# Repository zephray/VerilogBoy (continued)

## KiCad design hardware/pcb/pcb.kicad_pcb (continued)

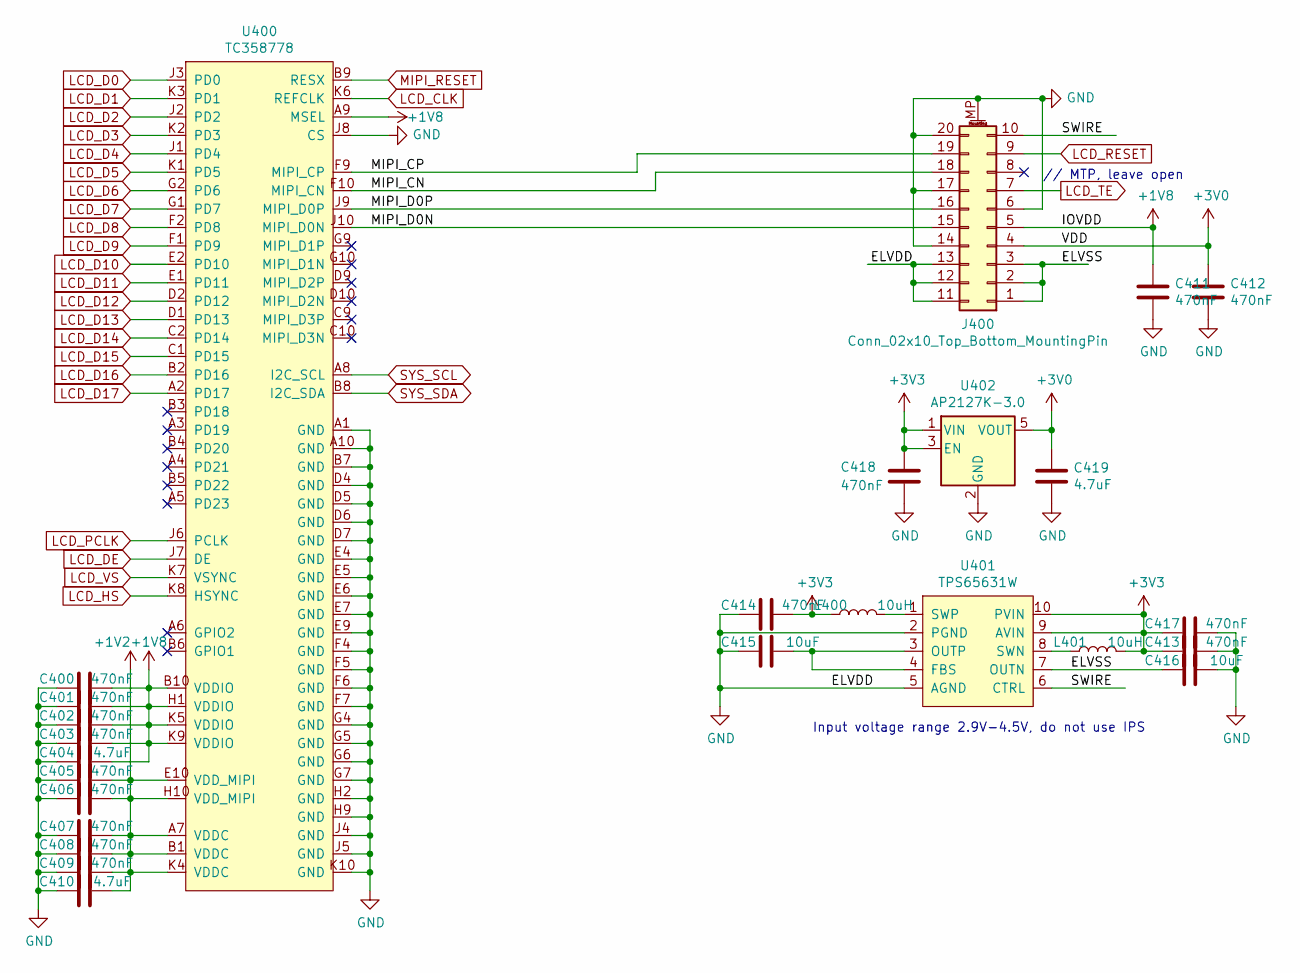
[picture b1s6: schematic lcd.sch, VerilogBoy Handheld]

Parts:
C400, C401, C402, C403, C405, C406, C407, C408, C409, C411, C412, C413, C414, C417, C418: 470nF; C_0402_1005Metric
C404, C410, C419: 4.7uF; C_0603_1608Metric
C415, C416: 10uF; C_0603_1608Metric
J400: Conn_02x10_Top_Bottom_MountingPin; AXE520124
L400, L401: 10uH; L_Vishay_IHLP-1212
U400: TC358778; BGA-80_10x10_7.0x7.0mm
U401: TPS65631W; DFN-10-1EP_3x3mm_P0.5mm_EP1.55x2.48mm
U402: AP2127K-3.0; SOT-23-5

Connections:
+1V2: C405.1, C406.1, C407.1, C408.1, C409.1, C410.1, U400.A7 (VDDC), U400.B1 (VDDC), U400.E10 (VDD_MIPI), U400.H10 (VDD_MIPI), U400.K4 (VDDC); also elsewhere on the board
+1V8: C400.1, C401.1, C402.1, C403.1, C404.1, C411.1, J400.5, U400.A9 (MSEL), U400.B10 (VDDIO), U400.H1 (VDDIO), U400.K5 (VDDIO), U400.K9 (VDDIO); also elsewhere on the board
+3V0: C412.1, C419.1, J400.4, U402.5 (VOUT)
+3V3: C413.2, C414.1, C417.2, C418.1, L400.1, L401.2, U401.9 (AVIN), U401.10 (PVIN), U402.1 (VIN), U402.3 (EN); also elsewhere on the board
/lcd/ELVSS: C416.2, J400.1, J400.2, J400.3, U401.7 (OUTN)
/lcd/MIPI_CN: J400.18, U400.F10 (MIPI_CN)
/lcd/MIPI_CP: J400.19, U400.F9 (MIPI_CP)
/lcd/MIPI_D0N: J400.15, U400.J10 (MIPI_D0N)
/lcd/MIPI_D0P: J400.16, U400.J9 (MIPI_D0P)
/lcd/SWIRE: J400.10, U401.6 (CTRL)
GND: C400.2, C401.2, C402.2, C403.2, C404.2, C405.2, C406.2, C407.2, C408.2, C409.2, C410.2, C411.2, C412.2, C413.1, C414.2, C415.2, C416.1, C417.1, C418.2, C419.2, J400.6, J400.11, J400.12, J400.13, J400.14, J400.17, J400.20, J400.MP (MountPin), U400.A1 (GND), U400.A10 (GND), U400.B7 (GND), U400.D4 (GND), U400.D5 (GND), U400.D6 (GND), U400.D7 (GND), U400.E4 (GND), U400.E5 (GND), U400.E6 (GND), U400.E7 (GND), U400.E9 (GND), U400.F4 (GND), U400.F5 (GND), U400.F6 (GND), U400.F7 (GND), U400.G4 (GND), U400.G5 (GND), U400.G6 (GND), U400.G7 (GND), U400.H2 (GND), U400.H9 (GND), U400.J4 (GND), U400.J5 (GND), U400.J8 (CS), U400.K10 (GND), U401.2 (PGND), U401.5 (AGND), U402.2 (GND); also elsewhere on the board
LCD_CLK: U400.K6 (REFCLK); also elsewhere on the board
LCD_D0: U400.J3 (PD0); also elsewhere on the board
LCD_D1: U400.K3 (PD1); also elsewhere on the board
LCD_D2: U400.J2 (PD2); also elsewhere on the board
LCD_D4: U400.J1 (PD4); also elsewhere on the board
LCD_D5: U400.K1 (PD5); also elsewhere on the board
LCD_D6: U400.G2 (PD6); also elsewhere on the board
LCD_D7: U400.G1 (PD7); also elsewhere on the board
LCD_D8: U400.F2 (PD8); also elsewhere on the board
LCD_D9: U400.F1 (PD9); also elsewhere on the board
LCD_D10: U400.E2 (PD10); also elsewhere on the board
LCD_D11: U400.E1 (PD11); also elsewhere on the board
LCD_D12: U400.D2 (PD12); also elsewhere on the board
LCD_D13: U400.D1 (PD13); also elsewhere on the board
LCD_D14: U400.C2 (PD14); also elsewhere on the board
LCD_D15: U400.C1 (PD15); also elsewhere on the board
LCD_D16: U400.B2 (PD16); also elsewhere on the board
LCD_D17: U400.A2 (PD17); also elsewhere on the board
LCD_DE: U400.J7 (DE); also elsewhere on the board
LCD_PCLK: U400.J6 (PCLK); also elsewhere on the board
LCD_RESET: J400.9; also elsewhere on the board
LCD_TE: J400.7; also elsewhere on the board
LCD_VS: U400.K7 (VSYNC); also elsewhere on the board
unnamed: C415.1, U401.3 (OUTP), U401.4 (FBS)
unnamed: L400.2, U401.1 (SWP)
unnamed: L401.1, U401.8 (SWN)
SYS_SCL: U400.A8 (I2C_SCL); also elsewhere on the board
SYS_SDA: U400.B8 (I2C_SDA); also elsewhere on the board

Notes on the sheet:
Input voltage range 2.9V-4.5V, do not use IPS
// MTP, leave open

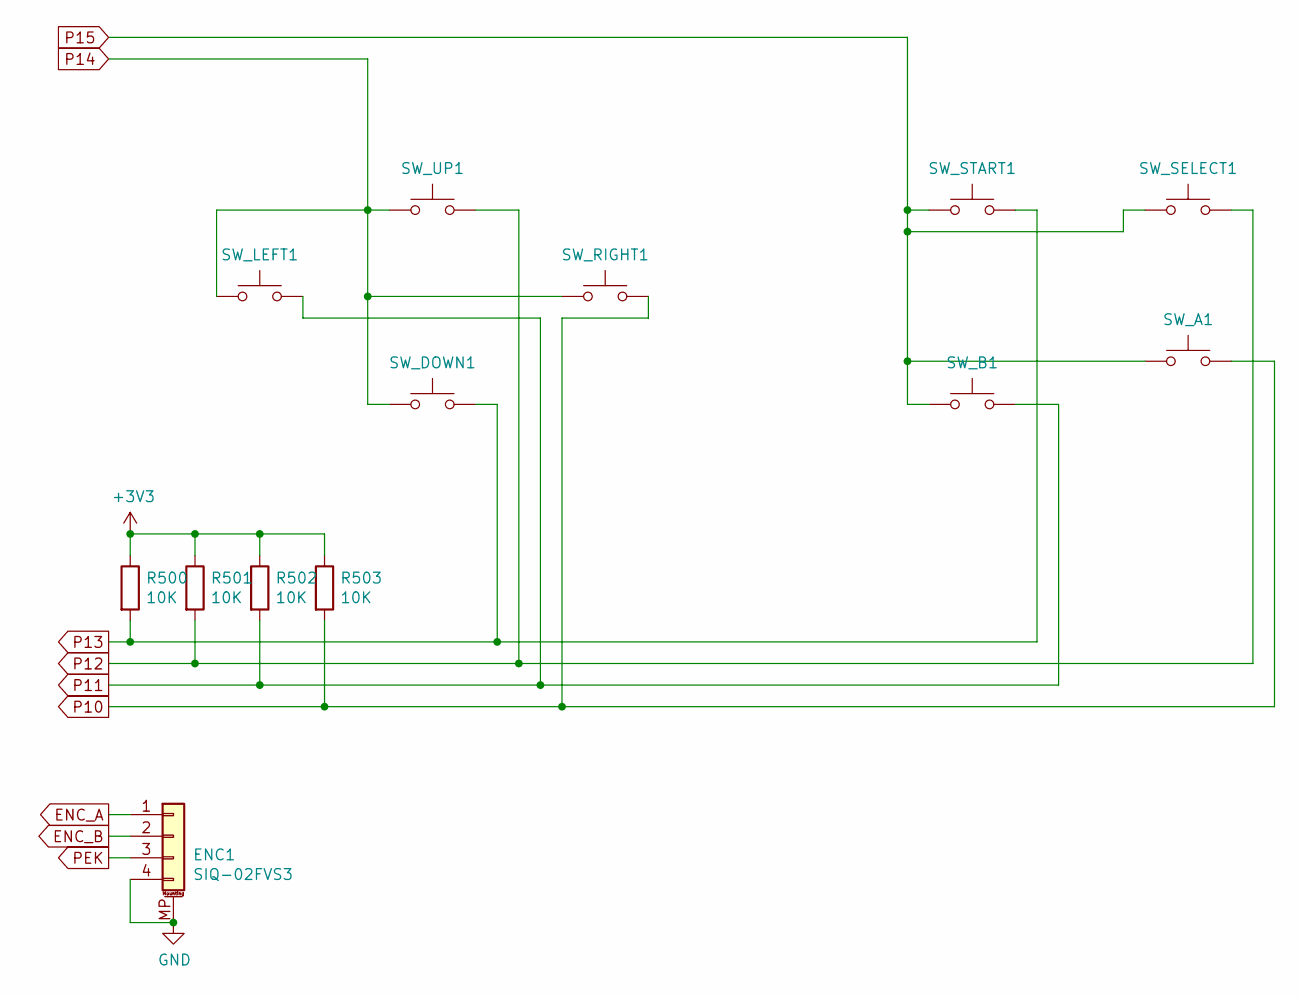
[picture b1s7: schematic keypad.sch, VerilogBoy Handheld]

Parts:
ENC1: SIQ-02FVS3
R500, R501, R502, R503: 10K; R_0402_1005Metric
SW_A1: SW_Push; Contact_4mm
SW_B1: SW_Push; Contact_4mm
SW_DOWN1: SW_Push; Contact_4mm
SW_LEFT1: SW_Push; Contact_4mm
SW_RIGHT1: SW_Push; Contact_4mm
SW_SELECT1: SW_Push; Contact_4mm
SW_START1: SW_Push; Contact_4mm
SW_UP1: SW_Push; Contact_4mm

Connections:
+3V3: R500.1, R501.1, R502.1, R503.1; also elsewhere on the board
ENC_A: ENC1.1; also elsewhere on the board
ENC_B: ENC1.2; also elsewhere on the board
GND: ENC1.4, ENC1.MP (MountPin); also elsewhere on the board
P10: R503.2, SW_A1.2, SW_RIGHT1.2; also elsewhere on the board
P11: R502.2, SW_B1.2, SW_LEFT1.2; also elsewhere on the board
P12: R501.2, SW_SELECT1.2, SW_UP1.2; also elsewhere on the board
P13: R500.2, SW_DOWN1.2, SW_START1.2; also elsewhere on the board
P14: SW_DOWN1.1, SW_LEFT1.1, SW_RIGHT1.1, SW_UP1.1; also elsewhere on the board
P15: SW_A1.1, SW_B1.1, SW_SELECT1.1, SW_START1.1; also elsewhere on the board
PEK: ENC1.3; also elsewhere on the board

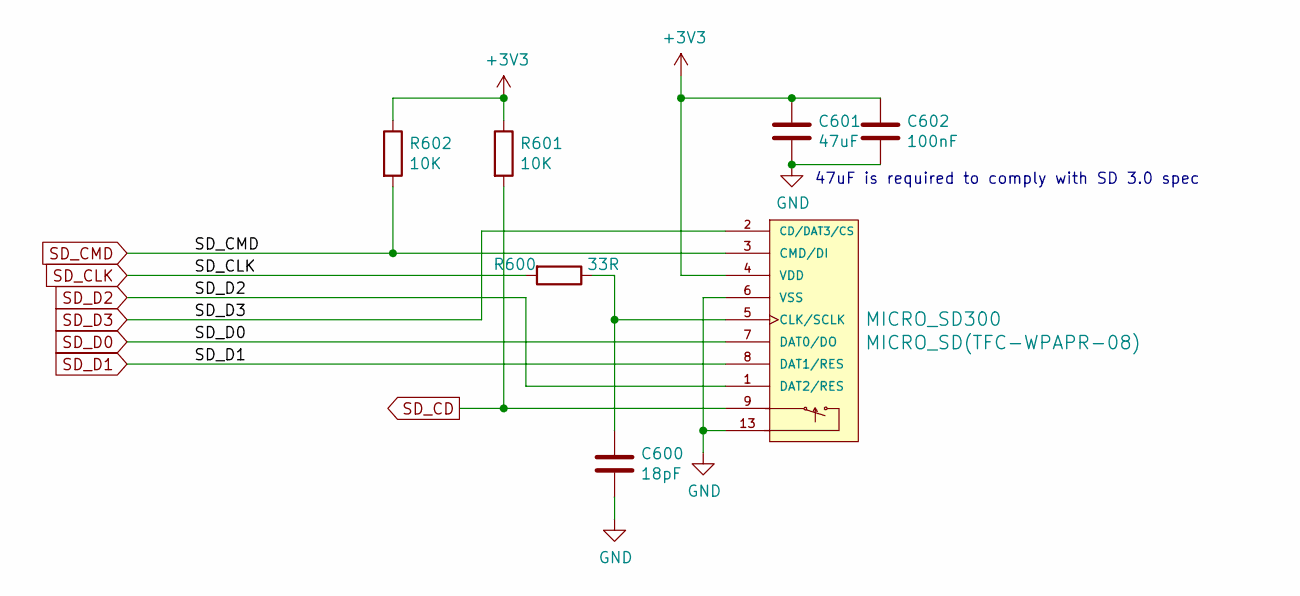
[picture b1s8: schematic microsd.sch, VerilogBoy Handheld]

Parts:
C600: 18pF; C_0402_1005Metric
C601: 47uF; C_0805_2012Metric
C602: 100nF; C_0402_1005Metric
MICRO_SD300: MICRO_SD(TFC-WPAPR-08); TFC-WPAPR-08
R600: 33R; R_0402_1005Metric
R601, R602: 10K; R_0402_1005Metric

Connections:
+3V3: C601.1, C602.1, MICRO_SD300.4 (VDD), R601.1, R602.1; also elsewhere on the board
GND: C600.2, C601.2, C602.2, MICRO_SD300.6 (VSS), MICRO_SD300.10, MICRO_SD300.11, MICRO_SD300.12, MICRO_SD300.13; also elsewhere on the board
unnamed: C600.1, MICRO_SD300.5 (CLK/SCLK), R600.1
SD_CD: MICRO_SD300.9, R601.2
SD_CLK: R600.2; also elsewhere on the board
SD_CMD: MICRO_SD300.3 (CMD/DI), R602.2; also elsewhere on the board
SD_D0: MICRO_SD300.7 (DAT0/DO); also elsewhere on the board
SD_D1: MICRO_SD300.8 (DAT1/RES); also elsewhere on the board
SD_D2: MICRO_SD300.1 (DAT2/RES); also elsewhere on the board
SD_D3: MICRO_SD300.2 (CD/DAT3/CS); also elsewhere on the board

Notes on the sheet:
47uF is required to comply with SD 3.0 spec

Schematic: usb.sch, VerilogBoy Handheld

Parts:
C700: 10uF; C_0603_1608Metric
C701: 100nF; C_0805_2012Metric
D700: B72590D0050H160; D_0402_1005Metric
J700: USB_B_Micro; USB_Micro-B_Amphenol_10103594-0001LF_Horizontal
R700: 1R; R_0603_1608Metric
R701: 0; R_0805_2012Metric
U700: USBLC6-2SC6; SOT-23-6

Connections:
GND: C701.2, D700.2 (A2), R700.2, R701.2, U700.2 (GND); also elsewhere on the board
unnamed: C700.2, R700.1
unnamed: C701.1, J700.5 (GND), J700.6 (Shield), R701.1
USB_DM: J700.2 (D-), U700.1 (IO1), U700.6 (IO1); also elsewhere on the board
USB_DP: J700.3 (D+), U700.3 (IO2), U700.4 (IO2); also elsewhere on the board
VBUS: C700.1, D700.1 (A1), J700.1 (VBUS); also elsewhere on the board

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
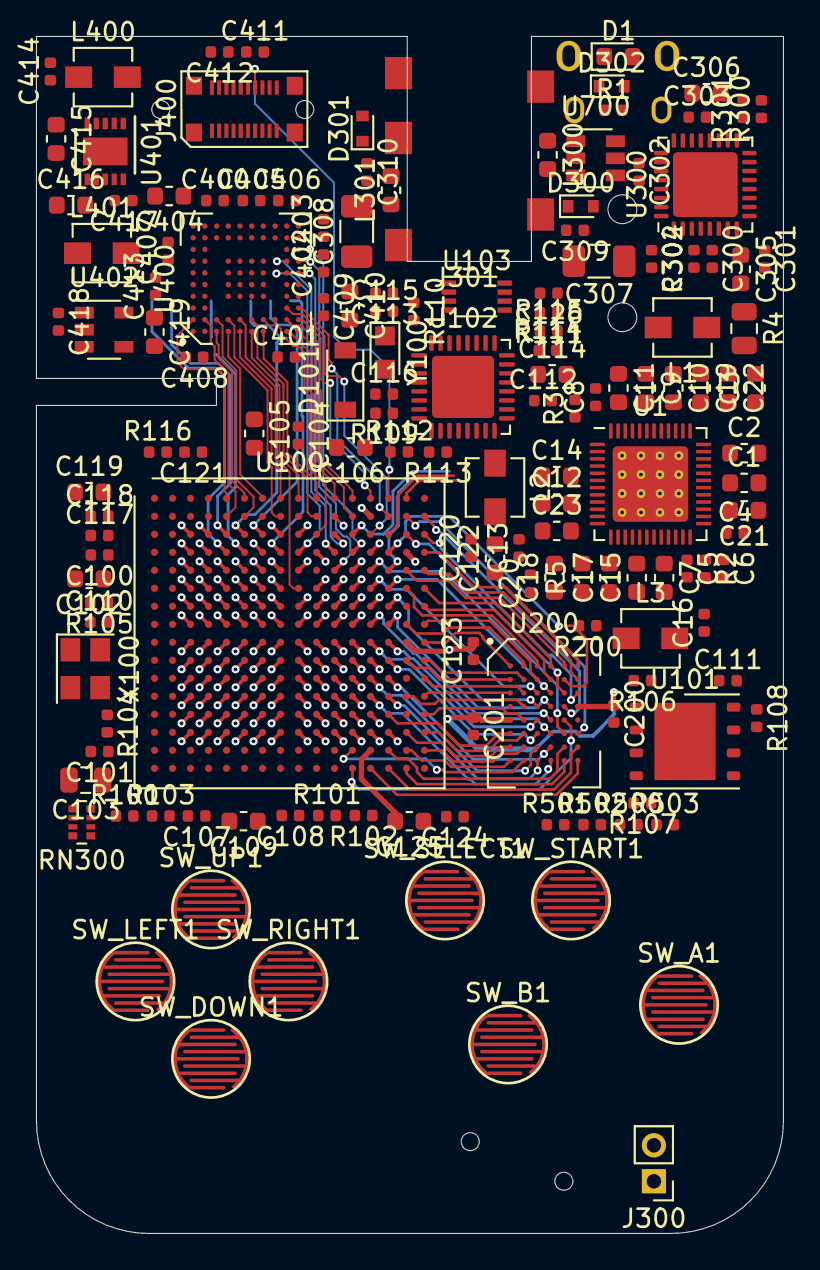
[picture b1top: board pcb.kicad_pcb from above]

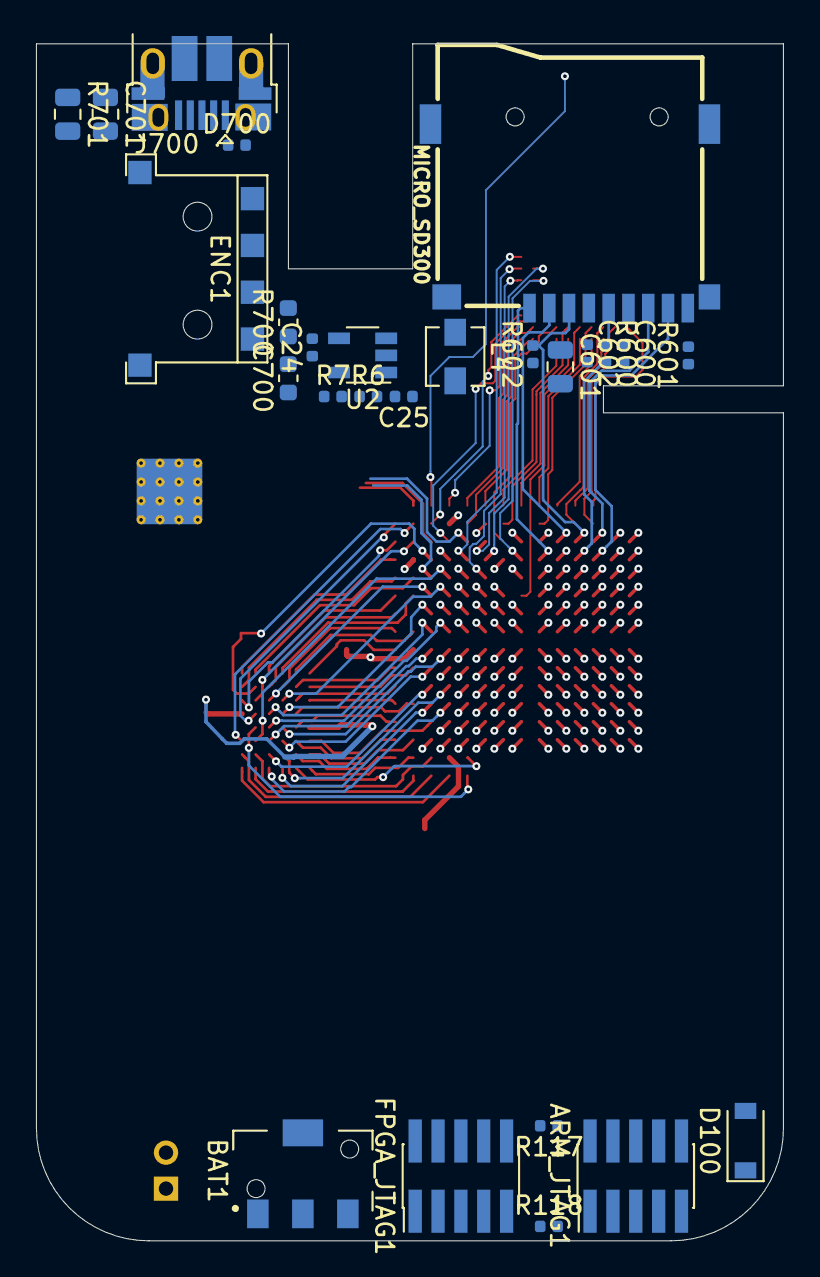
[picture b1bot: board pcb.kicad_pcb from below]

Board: 4 copper layers, 41.5 x 66.5 mm, 176 parts (26 on the bottom side), 179 nets.

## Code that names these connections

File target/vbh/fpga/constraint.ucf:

CONFIG VCCAUX=3.3;

NET CLK_IN LOC = N8;
NET CLK* IOSTANDARD = LVCMOS33;
NET CLK_IN TNM_NET = CLK_IN;
TIMESPEC TS_IN_CLK = PERIOD CLK_IN 40.7 ns HIGH 50%;

#NET MCU_CS LOC = T7;
#NET MCU_SCK LOC = P6;
#NET MCU_MISO LOC = T6;
#NET MCU_MOSI LOC = R5;
#NET MCU_IRQ LOC = T5;
#NET MCU* IOSTANDARD = LVCMOS33;

NET "SPI_CS_B"   LOC = T3  |IOSTANDARD = LVCMOS33;
NET "SPI_SCK"    LOC = R11 |IOSTANDARD = LVCMOS33;
NET "SPI_MOSI"   LOC = T10 |IOSTANDARD = LVCMOS33;
NET "SPI_MISO"   LOC = P10 |IOSTANDARD = LVCMOS33 | PULLUP;

NET RAM_DQ<0> LOC = E16;
NET RAM_DQ<1> LOC = C15;
NET RAM_DQ<2> LOC = C16;
NET RAM_DQ<3> LOC = B16;
NET RAM_DQ<4> LOC = T12;
NET RAM_DQ<5> LOC = E13;
NET RAM_DQ<6> LOC = B15;
NET RAM_DQ<7> LOC = T14;
NET RAM_DQ<8> LOC = K15;
NET RAM_DQ<9> LOC = M16;
NET RAM_DQ<10> LOC = L16;
NET RAM_DQ<11> LOC = M15;
NET RAM_DQ<12> LOC = N16;
NET RAM_DQ<13> LOC = P16;
NET RAM_DQ<14> LOC = N14;
NET RAM_DQ<15> LOC = P15;
NET RAM_A<0> LOC = F15;
NET RAM_A<1> LOC = F16;
NET RAM_A<2> LOC = E15;
NET RAM_A<3> LOC = H16;
NET RAM_A<4> LOC = G16;
NET RAM_A<5> LOC = F13;
NET RAM_A<6> LOC = G14;
NET RAM_A<7> LOC = F14;
NET RAM_A<8> LOC = R12;
NET RAM_A<9> LOC = M13;
NET RAM_A<10> LOC = M14;
NET RAM_A<11> LOC = T15;
NET RAM_A<12> LOC = L13;
NET RAM_A<13> LOC = L14;
NET RAM_A<14> LOC = K14;
NET RAM_A<15> LOC = J14;
NET RAM_A<16> LOC = H13;
NET RAM_A<17> LOC = H14;
NET RAM_A<18> LOC = R15;
NET RAM_A<19> LOC = R16;
NET RAM_A<20> LOC = T13;
NET RAM_A<21> LOC = J13;
NET RAM_LB_N LOC = J16;
NET RAM_UB_N LOC = K16;
NET RAM_OE_N LOC = H15;
NET RAM_CE_N LOC = D14;
NET RAM_WE_N LOC = R14;
NET RAM_ZZ_N LOC = D16;
NET RAM_DQ* PULLUP;
NET RAM* IOSTANDARD = LVCMOS18;

#NET SD_CLK LOC = B5;
#NET SD_CMD LOC = A5;
#NET SD_DAT<0> LOC = C5;
#NET SD_DAT<1> LOC = D5;
#NET SD_DAT<2> LOC = B6;
#NET SD_DAT<3> LOC = A6;
#NET SD* IOSTANDARD = LVCMOS33;

#NET DAC_BCLK LOC = B8;
#NET DAC_MCLK LOC = A8;
#NET DAC_DOUT LOC = C9;
#NET DAC_LRCK LOC = A9;
#NET DAC_SCK LOC = B10;
#NET DAC_SDA LOC = A10;
#NET DAC* IOSTANDARD = LVCMOS33;

NET BL_EN LOC = A11;
NET BL_PWM LOC = E10;
NET BL* IOSTANDARD = LVCMOS33;

#NET PMU_IRQ LOC = E11;
NET PMU_SCK LOC = C11 | PULLUP;
NET PMU_SDA LOC = D11 | PULLUP;
NET PMU* IOSTANDARD = LVCMOS33; 

NET LCD_TE LOC = C7;
NET LCD_TE IOSTANDARD = LVCMOS33;

NET LCD_RESET LOC = A14;
NET LCD_RESET IOSTANDARD = LVCMOS33;

NET LCD_D_LP_P LOC = F1;
NET LCD_D_LP_N LOC = D1;
NET LCD_D_LP* IOSTANDARD = LVCMOS18;
NET LCD_D_LP* DRIVE = 24;

NET LCD_D_HS_P LOC = E2;
NET LCD_D_HS_N LOC = E1;
//NET LCD_D_HS* IOSTANDARD = DIFF_HSTL_I_18;

NET LCD_C_LP_P LOC = C2;
NET LCD_C_LP_N LOC = B2;
NET LCD_C_LP* IOSTANDARD = LVCMOS18;
NET LCD_C_LP* DRIVE = 24;

NET LCD_C_HS_P LOC = C1;
NET LCD_C_HS_N LOC = B1;
//NET LCD_C_HS* IOSTANDARD = DIFF_HSTL_I_18;

NET KEY_IN<0> LOC = P8;
NET KEY_IN<1> LOC = T9;
NET KEY_IN<2> LOC = R9;
NET KEY_IN<3> LOC = P9;
NET KEY_OUT<0> LOC = P11;
NET KEY_OUT<1> LOC = P12;
NET KEY* IOSTANDARD = LVCMOS33;

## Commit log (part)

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2018-02-08 Working on DVI interface
2018-02-09 Porting CPU and DMA
2018-02-09 Add test ROM
2018-02-10 Add bin2mif for test ROM generation
2018-02-10 Fix bin2mif bug
2018-02-11 Add debugger and debug ROM
2018-02-11 Update documents
2018-02-13 Remove unused ipcores
2018-02-14 Ignore generated mif files
2018-02-14 Add chipscope and debug buttons
2018-02-15 Start working on PPU
2018-02-15 Add some design notes
2018-02-16 Working on PPU's bus logic and Pixel FIFO
2018-02-17 Start designing ppu's FSM
2018-02-17 Update some design notes
2018-02-17 Basic pixel fifo
2018-02-18 PPU pixel FIFO working
2018-02-18 Debugging PPU
2018-02-18 Full GameBoy Boot ROM ready
2018-02-18 Fix timing
2018-02-20 Adding basic NOR flash cartridge support
2018-02-22 Fix DVI timing constraint error
2018-02-24 Implement PPU Interrupt
2018-03-03 Add rom convertion script
2018-03-03 Add null joystick & ppu enable bit bug fix
2018-03-07 Implement OAM Search & Fix HV timing bug & Fix DVI timing bug & Implement #4
2018-03-08 Allow testbench running test ROM
2018-03-08 Fix PPU valid signal bug & Implement object rendering
2018-03-12 Fix #2
2018-03-15 Add support for SCX; Fix tile addressing bug
2018-03-16 Make OAM ram seq write & seq read
2018-03-16 Add MBC5 implementation
2018-03-16 Fix MBC race condition
2018-03-16 Fix pixel bit sequence bug
2018-03-16 Fix background tile addressing
2018-03-17 Fix #5
2018-03-31 Start working on the target hardware
2018-03-31 Add PADS library
2018-04-01 Initial layout
2018-04-02 Add expansion riser connector
2018-04-02 Add SD card slot
2018-04-08 Update lib
2018-04-09 Start working on sound part
2018-04-09 Fix project file
2018-04-09 Start implementing channel 3
2018-04-09 Supplement some header information
2018-04-09 Enable AC97 pins
2018-04-10 Relicense
2018-04-10 Style change
2018-04-12 Sound working
2018-04-13 Implementing DualShock2 driver
2018-04-14 Support timer
2018-04-15 Bug fixes
2018-04-15 Sprites can be rendered with "negative" coordinates
2018-04-15 Add some test results
2018-04-15 Fix horizontal timing
2018-04-15 Fix wave channel access and enable bug
2018-04-15 Update test results
2018-04-17 Dual Shock driver working
2018-04-18 Controller finished
2018-04-18 Fix timer bug
2018-04-19 Change LCD color map
2018-04-19 Add support for cartridge ram
2018-04-20 Use linear function for color map.
2018-04-20 Fix sprite rendering overlap bug
2018-04-20 Fix noise channel inferred latch bug
2018-04-20 Disable default breakpoint
2018-04-20 Fix window trigger position bug
2018-04-20 Finish STN effect emulation
2018-04-22 Fix timer interrupt bug
2018-04-22 Fix windows & object priority
2018-04-22 Add wait cycle for DMA operation
2018-04-26 Remove MCU related files for now
2018-04-29 Fix missing files
2018-06-21 start refactor
2018-06-21 cpu: start gathering information
2018-06-22 cpu: add instruction documents
2018-07-05 Fix wrong opcode for LD A, (rr)
2018-07-15 Clean up for refactoring
2018-07-16 initial framework
2018-07-17 doc: add bitwise and sp alu operations
2018-08-01 hardware: start designing the hardware
2018-08-02 hardware: add pmu
2018-08-11 hardware: verify footprints
2018-10-12 doc: revise cpu microarchitecture
2018-10-14 hardware: working on 3d models
2018-10-15 hardware: start designing case
2018-10-20 hardware: 3d model change
2018-10-20 hardware: adjust placement
2018-10-21 hardware: finializing schematics
2018-10-22 hardware: initial pcb layout
2018-10-22 hardware: minor case design change
2018-10-26 hardware: add key foam support structure
2018-10-28 hardware: finish pcb rev 1
2018-10-28 hardware: update converted file
2018-11-11 cpu: working on the core arch
2018-11-11 doc: sync with rtl code
2018-11-11 doc: handling multi-M-cycle instructions
2018-11-11 rtl: implementing EX-FSM
2018-11-18 doc: finish first cycle decoding table
2018-11-19 rtl: working on cpu logic
2018-11-19 readme: relicense simulation code
2018-11-20 rtl: bug fixes
2018-11-20 sim: implement basic simulation testbench
2018-11-20 sim: implement edge-triggering memory simulation
2018-11-21 doc: fix error & design change
2018-11-21 rtl: implement more instructions & bug fixes
2018-11-21 sim: modify debug output
2018-11-22 target-vb: import libopencm3
2018-11-23 target-vb: basic framework & add axp driver
2018-11-24 target-vbh: rename to vbh
2018-11-24 target-vbh: finish renaming
2018-11-24 target-vbh: implement mcu-fpga spi communication
2018-11-24 target-vbh: add fpga project
2018-11-29 target-vbh: import dsi-core by twlostow
2018-12-01 doc: add vb hardware ref manual
2018-12-01 target-vb: add pwm driver
2018-12-03 doc: update dsi controller register
2018-12-03 target-vbh: port dsicore IP
2018-12-06 target-vbh: implement mipi dsi driver
2018-12-09 Fix #12 Fix #11
2018-12-13 hardware: modify RAM connections
2018-12-21 hardware: pcb rev1a
2018-12-29 hardware: fix wrong inductor value
2019-01-02 rtl: fix 16bit imm loading
2019-01-03 sim: add sp display
2019-01-03 rtl: implement more instructions
2019-01-13 gitignore: ignore libreoffice temp files
2019-01-13 rtl: handle jr/jp/call
2019-01-13 target-vbh: integrating cpu into project
2019-01-15 rtl: rename top-level unit
2019-01-15 rtl: fix jr
2019-01-15 rom: working on boot rom
2019-01-16 target-vbh: modify for new hw rev
2019-01-19 rtl: fix ld, cb instructions
2019-01-20 rtl: support ld a, [hl+/-], bug fixes
2019-01-20 tools: update bin2mif build
2019-01-20 rtl: fix reg/wire definition errors
2019-01-20 rtl: fix signal width
2019-01-22 rtl: fix several instructions
2019-01-22 sim: quiet
2019-01-22 rom: implement dsi driver
2019-01-22 target-vbh: add brom
2019-01-25 bootrom: fix dsi driver
2019-01-25 rtl: fix rst; add builtin hram
2019-01-27 bootrom: fix dsi register setting
2019-01-27 target-vbh: mipi-dsi working
2019-01-27 rtl: support more instructions
2019-01-27 readme: update
2019-01-27 cpu: fix pc/sp inc/dec inside ct fsm
2019-02-02 hardware: add tc358778 to library
2019-02-02 readme: update hw-arch and running photo
2019-02-02 readme: use png to avoid compatibility issue
2019-02-02 doc: update hw arch figure
2019-02-03 hardware: fix #8 fix #6
2019-02-03 rtl: fix ise synthesis
2019-02-03 target-vbh: rename dsicore registers; support full sync mode
2019-02-06 rtl: support interrupt
2019-02-18 tools/bin2mif: add bit width option
2019-02-18 target-panog1: start porting to pano logic g1
2019-02-18 target-panog1: move rtl file into fpga directory
2019-02-18 target-panog1: firmware stub
2019-02-21 target-panog1: start working on LPDDR controller
2019-02-21 target-panog1: add LPDDR simulation model
2019-02-23 target-panog1: fix picorv32 simulation
2019-02-24 target-panog1: lpddr partially working
2019-02-24 rtl: fix wrong reg/wire type
2019-02-28 target-vbh: modify dsicore timing control
2019-03-01 target-panog1: support 32bit lpddr
2019-03-01 target-panog1: add unified cache for lpddr
2019-03-01 target-panog1: explicitly define wire type
2019-03-02 target-panog1: update memtest fw
2019-03-02 rtl: implement halt
2019-03-02 tools/bin2mif: support byte skip
2019-03-02 target-panog1: fix cache
2019-03-02 target-panog1: fix bin2mif path reference
2019-03-02 Fix compile for buggy GNU coreutils (8.28) see https://github.com/riscv/riscv-gcc/issues/120)
2019-03-02 target-panog1: fix ddr slew rate
2019-03-03 target-panog1/cache: remove lookahead, make 3 cycle cache optional
2019-03-03 target-panog1: allow spi booting
2019-03-03 target-panog1/fw: support spi boot, add dhrystone test
2019-03-03 target-panog1: update readme
2019-03-22 target-vbh: remove mcu fw; move softcore fw into target folder
2019-03-23 target-panog1: add wip usb support
2019-03-23 readme: restructure
2019-03-23 doc: update various documents
2019-03-23 target-panog1: enable usb in the rtl
2019-03-26 target-panog1: add simple uart tx
2019-03-26 target-panog1: change cache & bridge ready pulse to be only 1 cycle
2019-03-26 target-panog1: support hard fault
2019-03-26 sim: bump copyright
2019-03-26 target-panog1: usb enum working
2019-03-26 target-panog1: implement hard fault handler
2019-03-28 target-panog1: implement usb gamepad driver; implement usb int xfer list
2019-03-29 rtl: import ppu from master
2019-03-29 rtl: fix sub instruction
2019-03-29 sim: implement display simulation
2019-03-29 sim: implement mmr probe; integrate dispsim
2019-03-29 roms: add test roms
2019-03-30 roms: fix test roms
2019-03-30 rtl: bug fixes, mainly flags related
2019-03-30 sim: modify to work with unit test
2019-03-30 roms: scripts and tools for unit test
2019-03-30 rtl: fix rst instruction
2019-03-30 sim: main loop modify
2019-03-30 roms: fix buggy tests
2019-03-31 rtl: fix negative jr
2019-03-31 sim: add speed disp; allow disable bootrom
2019-03-31 rtl: add bootrom and dma
2019-03-31 roms: add more tests
2019-03-31 rtl: support timer
2019-03-31 sim: allow ignore halt
2019-04-03 target-panog1: usb mass storage working
2019-04-05 target/pano-g1: usb msd and fatfs working
2019-04-07 target-panog1: use spi xip for rv fw
2019-04-07 target-panog1: allow vbcore to access lpddr ram
2019-04-07 target-panog1: modify for xip; basic ui
2019-04-09 target-panog1: trying to fix github source code line count
2019-04-10 rtl: fix dma timing issue
2019-04-10 target-panog1: fw support audio; use polling for usb
2019-04-10 rtl: add sound support
2019-04-10 target-panog1: support sound
2019-04-12 cpu: fix interrupt dispatch
2019-04-13 rtl: replace one halt bug with another halt bug
2019-04-13 rtl: implement a dummy serial interface
2019-04-13 target-panog1: optimize ram usage
2019-04-13 target-panog1: change ram size; support mbc5
2019-04-13 rtl: fix sprite display bug; fix various width bugs
2019-04-14 rtl: fix unused mmio; add address bits attribute to single port ram
2019-04-14 target-panog1: adjust vga timing; add cartridge ram
2019-04-14 doc: update various readmes
2019-04-14 doc: fix wrong url to demo
2019-04-14 target-vbh: fix permissions; adjust dsi initialization
2019-04-16 rtl: fixed interrupt dispatch cancellation
2019-04-20 target-vbh: catch up
2019-04-21 target-vbh: implement vb to dsi mixing
2019-04-21 target-vbh: firmware catchup
2019-04-21 rtl: accuracy improvement
2019-04-21 readme: add test results; add vbh photo
2019-04-22 rtl: improve accuracy
2019-04-22 readme: update test results
2019-04-23 sim: allow multiple memories on bus
2019-04-25 rtl: fix interrupt timing
2019-05-30 target-panog1: fix irq addr mentioned in #20
2019-05-30 target-panog1: fix transfer length bug mentioned in #20
2019-08-12 USB fixes, now works with 3 devices it didn't work with before.
2019-08-12 Added support for programming SPI flash using xc3sprog. It's much faster than Impact since it can rewrite just the firmware image w/o rewritting the .bit image.
2019-08-12 Added .bit file missed in last commit.
2019-08-18 Increased hub power on delay to 1.5 seconds, fixes another USB flash drive. On a normal full system the timing isn't critical since an attached device can connect at any time following initialization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
2019-10-22 sim: remove lelf; add binary to ignore list
2019-10-22 test: fix simple unit tests
2019-10-22 fix Makefile scripts
2020-01-06 vbh: migrate to kicad
2020-01-07 vbh: pcb layout
2020-05-06 test: test conditional function call
2020-05-06 doc: fix typo
2020-05-06 sim: allow instruction level trace
2020-05-06 rtl: remove decoder rom
2020-05-06 rtl: buffer control signals with FF
2020-06-06 rtl: control unit should respond to reset on any posedge of clock
2020-06-06 rtl: fix mem to reg alu double writeback
2020-06-07 rtl: fix flags update in mem to reg alu instructions
2020-06-07 sim: support mbc simulation
2020-06-07 rtl: fix halt handling
2020-06-07 sim: fix mbc3 rom banking handling
2020-06-07 readme: update the regression caused by recent control unit change
2020-06-08 rtl: fix if register readout
2020-06-08 readme: reflect recent rtl change
2020-06-10 pcb: working on ram/ lcd routing
2020-06-11 pcb: routing lcd section
2021-01-09 rtl/sim: compiling fixes
2021-01-10 rtl: fix various interrupt handling edge cases
2021-01-10 sim: initialize tick count
2021-01-10 rtl: use sync reset
2021-01-10 remove vbh related stuff, moved to another repo
2021-12-08 Fix PPU bug where PPU is supposed to enter mode 0 on disable
2022-12-09 rtl: use single clock for sound
